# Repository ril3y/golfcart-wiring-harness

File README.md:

# Golf Cart Wiring Harness

A KiCad project for designing a golf cart wiring harness with CAN bus communication and microcontroller integration.

## Project Overview

This project contains the complete KiCad design files for a golf cart wiring harness system that includes:

- Microcontroller-based control unit
- CAN bus communication interface
- Wire harness connector layouts
- PCB design for control electronics

## Files Structure

```
wire_harness/
├── wire_harness.kicad_pro     # Main project file
├── wire_harness.kicad_sch     # Main schematic
├── mcu-can.kicad_sch          # MCU and CAN interface schematic
├── wire_harness.kicad_pcb     # PCB layout
├── plots/                     # Generated gerber files and plots
└── wire_harness-backups/      # Automatic project backups
```

## Documentation

### Schematic
[View Schematic (PDF)](./schematic.pdf)

### PCB Layout
[View PCB Layout (PDF)](./pcb.pdf)

## Production

- **PCB Order Number**: W2025101705278993
- **PCB Order Date**: October 17, 2025
- **Tag**: `production-W2025101705278993`

## Generated Files

The `plots/` directory contains manufacturing files:
- Gerber files for PCB fabrication
- Drill files for hole placement
- Pick and place files
- Bill of materials

## KiCad Version

This project was created with KiCad 9.0.

## License

This project is open source hardware. Feel free to modify and use for your own golf cart projects.

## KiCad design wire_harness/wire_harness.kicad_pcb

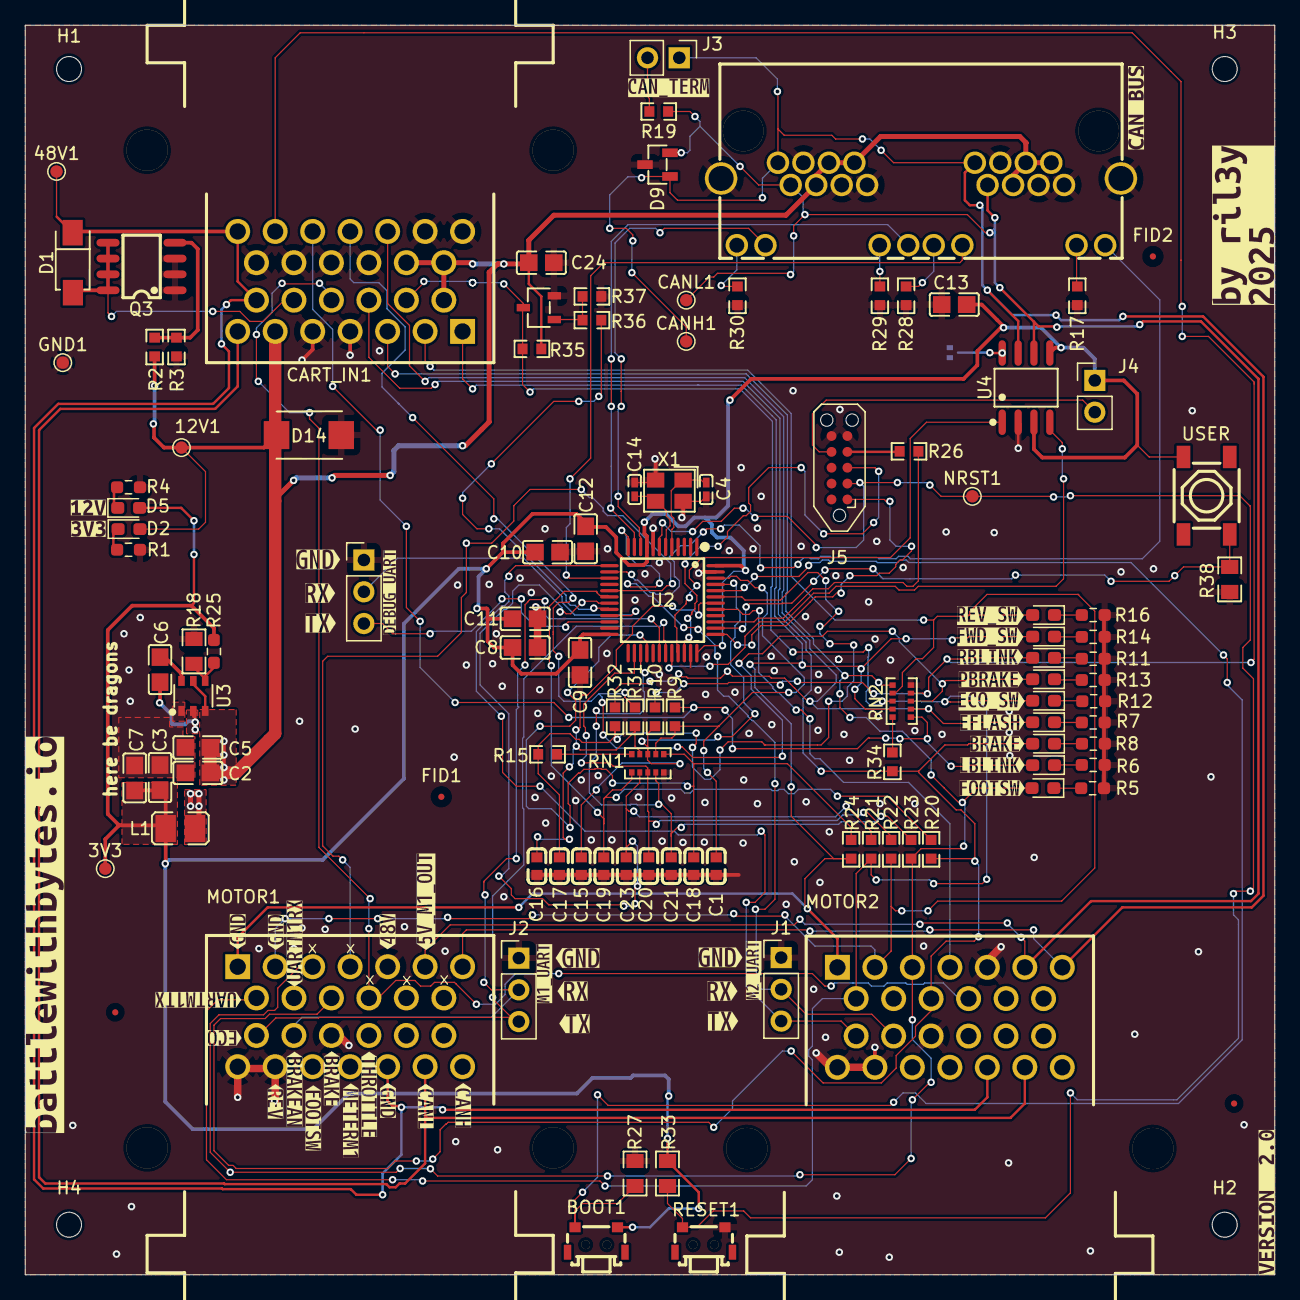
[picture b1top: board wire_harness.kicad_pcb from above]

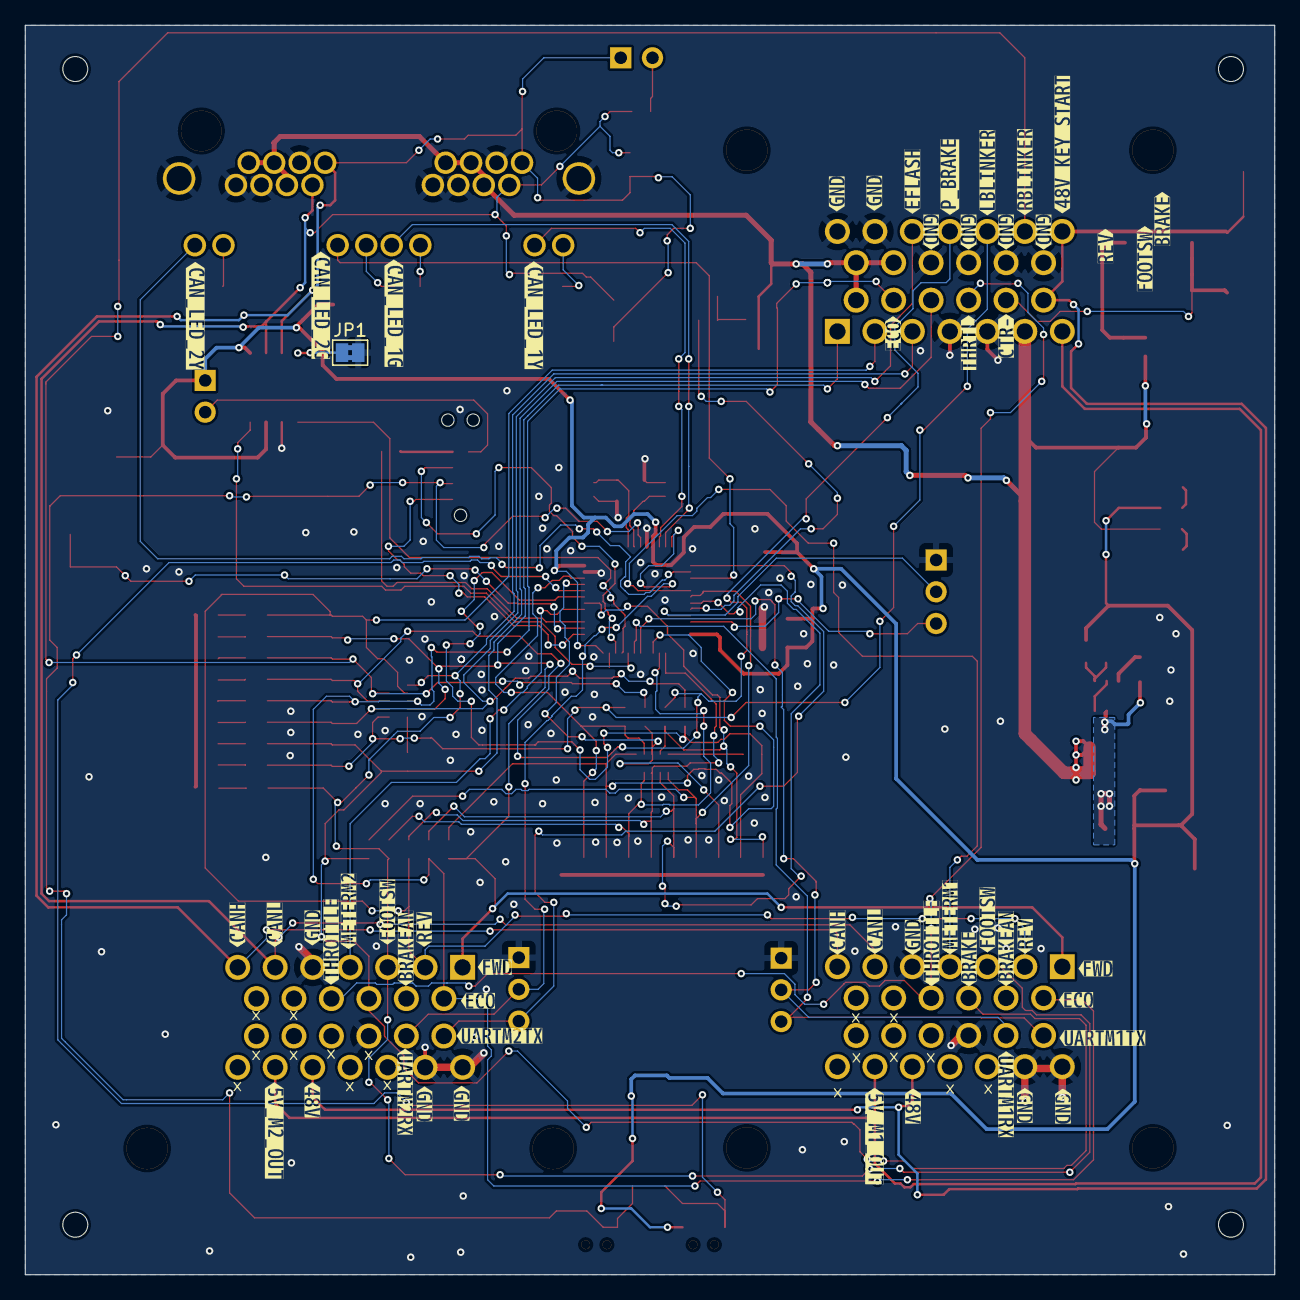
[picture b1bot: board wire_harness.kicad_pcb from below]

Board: 2 copper layers, 100.0 x 100.0 mm, 211 parts (55 on the bottom side), 76 nets.

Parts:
3V3: 3V3; TestPoint_Pad_D1.0mm
12V1: 12V; TestPoint_Pad_D1.0mm
48V1: 48V; TestPoint_Pad_D1.0mm
BOOT1: 1TS003B-1400-3500A; KEY-SMD_1TS003B
C1, C15, C16, C17, C18, C19, C20, C21, C23: .1uF; C0603
C2, C12: 10uF; C0805
C3, C7, C24: 22uF; C0805
C4, C14: 12pF; C0402
C5, C6, C8, C9, C10, C11, C13: .1uf; C0805
CANH1: CANH; TestPoint_Pad_D1.0mm
CANL1: CANL; TestPoint_Pad_D1.0mm
CART_IN1: 9-6437287-8; CONN-TH_9-6437287-8
D1: SS510_C513471; SMA_L4.3-W2.6-LS5.0-RD
D2: 12V PWR; LED_0603_1608Metric_Pad1.05x0.95mm_HandSolder
D3, D4, D6, D7, D8, D10, D11, D13: LED; LED_0603_1608Metric_Pad1.05x0.95mm_HandSolder
D5: 3V3 PWR; LED_0603_1608Metric_Pad1.05x0.95mm_HandSolder
D9: SM712_C521963; SOT-23-3_L2.9-W1.3-P1.90-LS2.4-BR
D12: RBLINKLED; LED_0603_1608Metric_Pad1.05x0.95mm_HandSolder
D14: SMBJ18CA; SMB_L4.6-W3.6-LS5.3-BI
FID1, FID2, FID3, FID4: Fiducial; Fiducial_0.5mm_Mask1.5mm
GND1: GND; TestPoint_Pad_D1.0mm
H1, H2, H3, H4: MountingHole; MountingHole_2mm
J1: M2 UART; PinHeader_1x03_P2.54mm_Vertical
J2: M1 UART; PinHeader_1x03_P2.54mm_Vertical
J3: TERM; PinHeader_1x02_P2.54mm_Vertical
J4: PWR; PinHeader_1x02_P2.54mm_Vertical
J5: TC2050-IDC; Tag-Connect_TC2050-IDC-NL_2x05_P1.27mm_Vertical
J6: DEBUG; PinHeader_1x03_P2.54mm_Vertical
JP1: SolderJumper_2_Bridged; SolderJumper-2_P1.3mm_Bridged2Bar_Pad1.0x1.5mm
L1: 2.2uH; L1008
MOTOR1, MOTOR2: 9-6437287-8; CONN-TH_9-6437287-8
NRST1: NRST; TestPoint_Pad_D1.0mm
Q1: BSS138; SOT-23-3_L2.9-W1.6-P1.90-LS2.8-BR
Q3: IRF7493TRPBF; SOP-8_L4.9-W3.9-P1.27-LS6.0-BL
R1: 4.7k; R_0603_1608Metric_Pad0.98x0.95mm_HandSolder
R2, R15, R34, R35: 10k; R0603
R3: 100K; R0603
R4, R5, R6, R7, R8, R11, R12, R13, R14, R16: 1k; R_0603_1608Metric_Pad0.98x0.95mm_HandSolder
R9, R10, R20, R21, R22, R23, R24, R31, R32: 34k; R0603
R17, R28, R29, R30, R36: 220; R0603
R18, R27, R33, R38: 10k; R0805
R19, R26: 120; R0603
R25: 33k; R_0603_1608Metric_Pad0.98x0.95mm_HandSolder
R37: 100k; R0603
RESET1: 1TS003B-1400-3500A; KEY-SMD_1TS003B
RN1, RN2: 10k; RES-ARRAY-SMD_1206-L3.2-W1.6-P0.64
U2: STM32F103C8T6; LQFP-48_L7.0-W7.0-P0.50-LS9.0-BL
U3: TPS561208DDCR; TSOT-23-6_L2.9-W1.6-P0.95-LS2.8-BR
U4: SN65HVD230DR; SOIC-8_L4.9-W3.9-P1.27-LS6.0-BL
U5: HC-RJ45-5JA-2-2; RJ45-TH_HCTL_HC-RJ45-5JA-2-2-Y
USER: 4*4*1.7; SW-SMD_4P-L5.2-W5.2-P3.70-LS6.5
X1: 7B008000F01; CRYSTAL-SMD_4P-L3.2-W2.5-BL
kibuzzard-68F14D91: G***; kibuzzard-68F14D91
kibuzzard-68F14E9F: G***; kibuzzard-68F14E9F
kibuzzard-68F14ED2: G***; kibuzzard-68F14ED2
kibuzzard-68F129BA: G***; kibuzzard-68F129BA
kibuzzard-68F134A4, kibuzzard-68F134A4#2: G***; kibuzzard-68F134A4
kibuzzard-68F134DA: G***; kibuzzard-68F134DA
kibuzzard-68F137E9: G***; kibuzzard-68F137E9
kibuzzard-68F137F1: G***; kibuzzard-68F137F1
kibuzzard-68F137FA: G***; kibuzzard-68F137FA
kibuzzard-68F138FC: G***; kibuzzard-68F138FC
kibuzzard-68F1349C, kibuzzard-68F1349C#2: G***; kibuzzard-68F1349C
kibuzzard-68F1381A: G***; kibuzzard-68F1381A
kibuzzard-68F1394E: G***; kibuzzard-68F1394E
kibuzzard-68F1395A: G***; kibuzzard-68F1395A
kibuzzard-68F13268: G***; kibuzzard-68F13268
kibuzzard-68F13492, kibuzzard-68F13492#2: G***; kibuzzard-68F13492
kibuzzard-68F13943: G***; kibuzzard-68F13943
kibuzzard-68F13965: G***; kibuzzard-68F13965
kibuzzard-685E9542: G***; kibuzzard-685E9542
kibuzzard-685E9548: G***; kibuzzard-685E9548
kibuzzard-685E9594: G***; kibuzzard-685E9594
kibuzzard-6861DCA1: G***; kibuzzard-6861DCA1
kibuzzard-6861DCF7: G***; kibuzzard-6861DCF7
kibuzzard-6876FB65: G***; kibuzzard-6876FB65
kibuzzard-68782A08, kibuzzard-68782A08#2, kibuzzard-68782A08#3: G***; kibuzzard-68782A08
kibuzzard-68782ACC, kibuzzard-68782ACC#2, kibuzzard-68782ACC#3: G***; kibuzzard-68782ACC
kibuzzard-68782B3B: G***; kibuzzard-68782B3B
kibuzzard-68782B6B, kibuzzard-68782B6B#2: G***; kibuzzard-68782B6B
kibuzzard-68782B7F, kibuzzard-68782B7F#2, kibuzzard-68782B7F#3: G***; kibuzzard-68782B7F
kibuzzard-68782B8A, kibuzzard-68782B8A#2, kibuzzard-68782B8A#3: G***; kibuzzard-68782B8A
kibuzzard-68782B9B, kibuzzard-68782B9B#2: G***; kibuzzard-68782B9B
kibuzzard-68782B26, kibuzzard-68782B26#2, kibuzzard-68782B26#3: G***; kibuzzard-68782B26
kibuzzard-68782B56, kibuzzard-68782B56#2: G***; kibuzzard-68782B56
kibuzzard-68782BAF: G***; kibuzzard-68782BAF
kibuzzard-68782BD3, kibuzzard-68782BD3#2: G***; kibuzzard-68782BD3
kibuzzard-68782BE1, kibuzzard-68782BE1#2, kibuzzard-68782BE1#3: G***; kibuzzard-68782BE1
kibuzzard-68782BF2, kibuzzard-68782BF2#2, kibuzzard-68782BF2#3: G***; kibuzzard-68782BF2
kibuzzard-68782C3E: G***; kibuzzard-68782C3E
kibuzzard-68782C4C, kibuzzard-68782C4C#2: G***; kibuzzard-68782C4C
kibuzzard-68782C17, kibuzzard-68782C17#2: G***; kibuzzard-68782C17
kibuzzard-68782C24: G***; kibuzzard-68782C24
kibuzzard-68782C33, kibuzzard-68782C33#2, kibuzzard-68782C33#3: G***; kibuzzard-68782C33
kibuzzard-68782F7C: G***; kibuzzard-68782F7C
kibuzzard-68805E5A: G***; kibuzzard-68805E5A
kibuzzard-68805E6D: G***; kibuzzard-68805E6D
kibuzzard-68805E53: G***; kibuzzard-68805E53
kibuzzard-68805E74: G***; kibuzzard-68805E74
kibuzzard-68805F7D: G***; kibuzzard-68805F7D
kibuzzard-68805F52: G***; kibuzzard-68805F52
kibuzzard-68805F93: G***; kibuzzard-68805F93
kibuzzard-68805FB4: G***; kibuzzard-68805FB4
kibuzzard-687828AA, kibuzzard-687828AA#2, kibuzzard-687828AA#3, kibuzzard-687828AA#4: G***; kibuzzard-687828AA
kibuzzard-688044A1: G***; kibuzzard-688044A1
kibuzzard-6878289E: G***; kibuzzard-6878289E
kibuzzard-68782841, kibuzzard-68782841#2: G***; kibuzzard-68782841
kibuzzard-68782877: G***; kibuzzard-68782877
kibuzzard-68782896: G***; kibuzzard-68782896
kibuzzard-68782918, kibuzzard-68782918#2, kibuzzard-68782918#3, kibuzzard-68782918#4, kibuzzard-68782918#5, kibuzzard-68782918#6, kibuzzard-68782918#7, kibuzzard-68782918#8, kibuzzard-68782918#9: G***; kibuzzard-68782918
kibuzzard-68782976: G***; kibuzzard-68782976
kibuzzard-68782984: G***; kibuzzard-68782984
kibuzzard-68782990: G***; kibuzzard-68782990

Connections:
3V3: 3V3.1, BOOT1.1, C3.2, C7.2, C8.2, C9.2, C10.2, C11.2, C12.1, C13.1, D5.2 (A), J4.1, L1.1, R25.2, R33.2, U2.9 (VDDA), U2.24 (VDD_1), U2.36 (VDD_2), U2.48 (VDD_3), U4.3 (VCC), U4.5 (VREF), USER.2
5V_OUT_M1: CART_IN1.7, MOTOR1.25, MOTOR2.25
12V: 12V1.1, C2.2, C5.2, C24.2, CART_IN1.6, CART_IN1.8, CART_IN1.14, CART_IN1.15, D2.2 (A), D14.1 (K), R2.1, R35.2, U3.3 (VIN), U3.5 (EN), U5.4, U5.5, U5.7, U5.12, U5.13, U5.15
48V_KEY_START: 48V1.1, CART_IN1.13, CART_IN1.26, D1.1 (K), MOTOR1.24, MOTOR2.24
BOOT: BOOT1.2, R27.2, U2.44 (BOOT0)
BRAKE_12V_IN: CART_IN1.10, D4.2 (A), MOTOR1.10, MOTOR2.10, R20.1, R34.2
BRAKE_UC_IN: C19.2, R20.2, RN1.1, U2.18 (PB0)
CAN_H: CANH1.1, D9.1, J3.1, MOTOR1.7, MOTOR2.7, U4.7 (CANH), U5.1, U5.9
CAN_L: CANL1.1, D9.2, MOTOR1.6, MOTOR2.6, R19.2, U4.6 (CANL), U5.2, U5.10
CAN_LED_1_G: U2.11 (PA1), U5.20
CAN_LED_1_Y: U2.10 (PA0-WKUP), U5.18
CAN_LED_2_G: U2.15 (PA5), U5.22
CAN_LED_2_Y: U2.14 (PA4), U5.24
CAN_RX: U2.32 (PA11), U4.4 (R)
CAN_TX: U2.33 (PA12), U4.1 (D)
CONTACTOR_NEG: CART_IN1.12, D1.2 (A), Q3.5 (D), Q3.6 (D), Q3.7 (D), Q3.8 (D)
ECO_12V_IN: CART_IN1.9, D6.2 (A), MOTOR1.8, MOTOR2.8, Q1.3 (D), R21.1, R35.1, RN2.8
ECO_12V_IN_UC_GATE: R36.2, U2.20 (PB2)
ECO_UC_IN: C23.2, R21.2, RN1.2, U2.19 (PB1)
EFLASH_12V_IN: CART_IN1.22, D11.2 (A), R32.2, RN2.2
EFLASH_UC_IN: C17.1, R15.2, R32.1, U2.43 (PB7)
FOOTSW_12V_IN: CART_IN1.3, D3.2 (A), MOTOR1.3, MOTOR2.3, R23.1, RN2.6
FOOTSW_UC_IN: C21.2, R23.2, RN1.4, U2.27 (PB14)
FWD_12V_IN: CART_IN1.1, D7.2 (A), MOTOR1.1, MOTOR2.1, R24.2, RN2.9
FWD_UC_IN: C18.2, R24.1, RN1.6, U2.28 (PB15)
GND: C1.1, C2.1, C3.1, C4.2, C5.1, C7.1, C8.1, C9.1, C10.1, C11.1, C12.2, C13.2, C14.1, C15.1, C16.2, C17.2, C18.1, C19.1, C20.1, C21.1, C23.1, C24.1, CART_IN1.4, CART_IN1.5, CART_IN1.16, CART_IN1.17, CART_IN1.18, CART_IN1.19, CART_IN1.20, CART_IN1.21, D9.3, D14.2 (A), GND1.1, J1.1, J2.1, J5.5, J5.6, J6.1, JP1.2 (B), MOTOR1.5, MOTOR1.16, MOTOR1.20, MOTOR1.21, MOTOR2.5, MOTOR2.16, MOTOR2.20, MOTOR2.21, Q1.2 (S), Q3.1 (S), Q3.2 (S), Q3.3 (S), R1.2, R3.2, R4.2, R5.2, R6.2, R7.2, R8.2, R11.2, R12.2, R13.2, R14.2, R16.2, R17.2, R18.1, R27.1, R28.2, R29.2, R30.2, R37.2, R38.1, RESET1.1, RN1.5, RN2.5, U2.8 (VSSA), U2.23 (VSS_1), U2.35 (VSS_2), U2.47 (VSS_3), U3.1 (GND), U4.2 (GND), U5.3, U5.6, U5.8, U5.11, U5.14, U5.16, U5.25, U5.26, X1.2 (GND), X1.4 (GND)
LBLINK_12V_IN: CART_IN1.24, D10.2 (A), R9.2, RN2.1
LBLINK_UC_IN: C1.2, R9.1, RN1.7, U2.46 (PB9)
M1_UART_RX: J2.2, MOTOR1.15, U2.30 (PA9)
M1_UART_TX: J2.3, MOTOR1.14, U2.31 (PA10)
M2_UART_RX: J1.2, MOTOR2.15, U2.12 (PA2)
M2_UART_TX: J1.3, MOTOR2.14, U2.13 (PA3)
METER_M1: MOTOR1.4, U2.17 (PA7)
METER_M2: MOTOR2.4, U2.41 (PB5)
NRST: J5.2, NRST1.1, R33.1, RESET1.2, U2.7 (NRST)
unnamed: D2.1 (K), R1.1
unnamed: D3.1 (K), R5.1
unnamed: D4.1 (K), R8.1
unnamed: D5.1 (K), R4.1
unnamed: D6.1 (K), R12.1
unnamed: D7.1 (K), R14.1
unnamed: D8.1 (K), R16.1
unnamed: D10.1 (K), R6.1
unnamed: D11.1 (K), R7.1
unnamed: D12.1 (K), R11.1
unnamed: D13.1 (K), R13.1
unnamed: J3.2, R19.1
unnamed: J4.2, J5.7
unnamed: J5.4, R26.1
unnamed: JP1.1 (A), U4.8 (RS)
unnamed: Q1.1 (G), R36.1, R37.1
unnamed: Q3.4 (G), R2.2, R3.1
unnamed: R15.1, RN1.10
unnamed: R17.1, U5.23
unnamed: R28.1, U5.21
unnamed: R29.1, U5.19
unnamed: R30.1, U5.17
unnamed: R34.1, RN2.10
unnamed: C6.1, U3.6 (VBST)
unnamed: R18.2, R25.1, U3.4 (VFB)
OSC_IN: C4.1, U2.5 (PD0-OSC_IN), X1.1 (IN)
OSC_OUT: C14.2, U2.6 (PD1-OSC_OUT), X1.3 (OUT)
PBRAKE_12V_IN: CART_IN1.23, D13.2 (A), R31.2, RN2.3
PBRAKE_UC_IN: C16.1, R31.1, RN1.9, U2.42 (PB6)
RBLINK_12V_IN: CART_IN1.25, D12.2 (A), R10.2, RN2.4
RBLINK_UC_IN: C15.2, R10.1, RN1.8, U2.45 (PB8)
REVSW_12V_IN: CART_IN1.2, D8.2 (A), MOTOR1.2, MOTOR2.2, R22.1, RN2.7
REV_UC_IN: C20.2, R22.2, RN1.3, U2.26 (PB13)
SWCLK: J5.1, U2.37 (PA14)
SWDIO: J5.3, U2.34 (PA13)
SWNODE: C6.2, L1.2, U3.2 (SW)
SWO: R26.2, U2.39 (PB3)
THROTTLE: CART_IN1.11, MOTOR1.11, MOTOR2.11
UART3_RX: J6.2, U2.21 (PB10)
UART3_TX: J6.3, U2.22 (PB11)
USER_BTN_IN: R38.2, U2.38 (PA15), USER.3

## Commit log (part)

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2025-06-30 Add README.md with project documentation and PDF schematics
2025-07-26 v2 updates: Modified KiCad schematics and PCB layout, updated backups
2025-07-26 Minor updates: permissions and schematic labels
2025-07-26 Update KiCad files and backups
2025-10-16 Add .claude/ to .gitignore to exclude Claude Code settings from version control
2025-10-16 Remove .claude/ files from version control
